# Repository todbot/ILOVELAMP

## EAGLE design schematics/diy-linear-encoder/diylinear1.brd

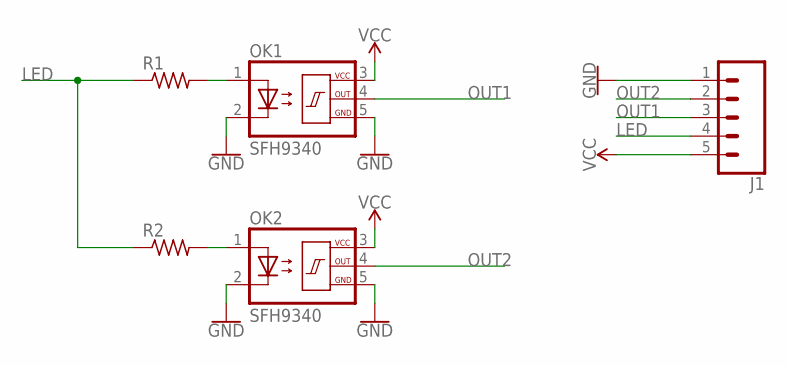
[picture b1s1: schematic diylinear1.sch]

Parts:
J1: CONN_05; 1X05
OK1, OK2: SFH9340
R1, R2: R-US_0204/5; 0204/5

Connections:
GND: J1.1, OK1.2 (C), OK1.5 (GND), OK2.2 (C), OK2.5 (GND)
LED: J1.4, R1.1, R2.1
unnamed: OK1.1 (A), R1.2
unnamed: OK2.1 (A), R2.2
OUT1: J1.3, OK1.4 (OUT)
OUT2: J1.2, OK2.4 (OUT)
VCC: J1.5, OK1.3 (VCC), OK2.3 (VCC)

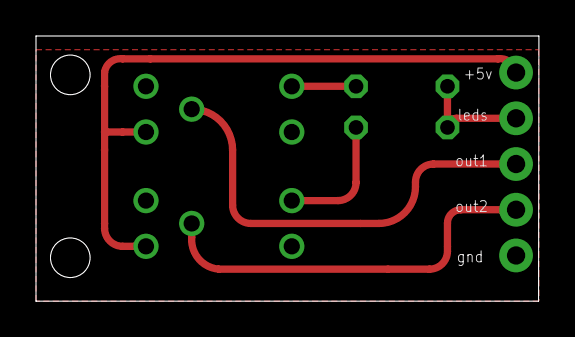
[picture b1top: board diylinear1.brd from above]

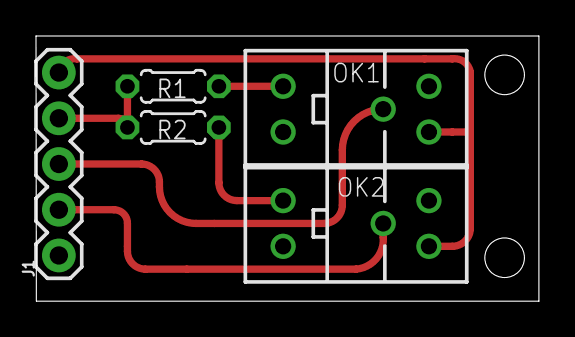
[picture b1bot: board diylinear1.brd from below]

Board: 2 copper layers, 27.9 x 14.7 mm, 5 parts (5 on the bottom side), 7 nets.

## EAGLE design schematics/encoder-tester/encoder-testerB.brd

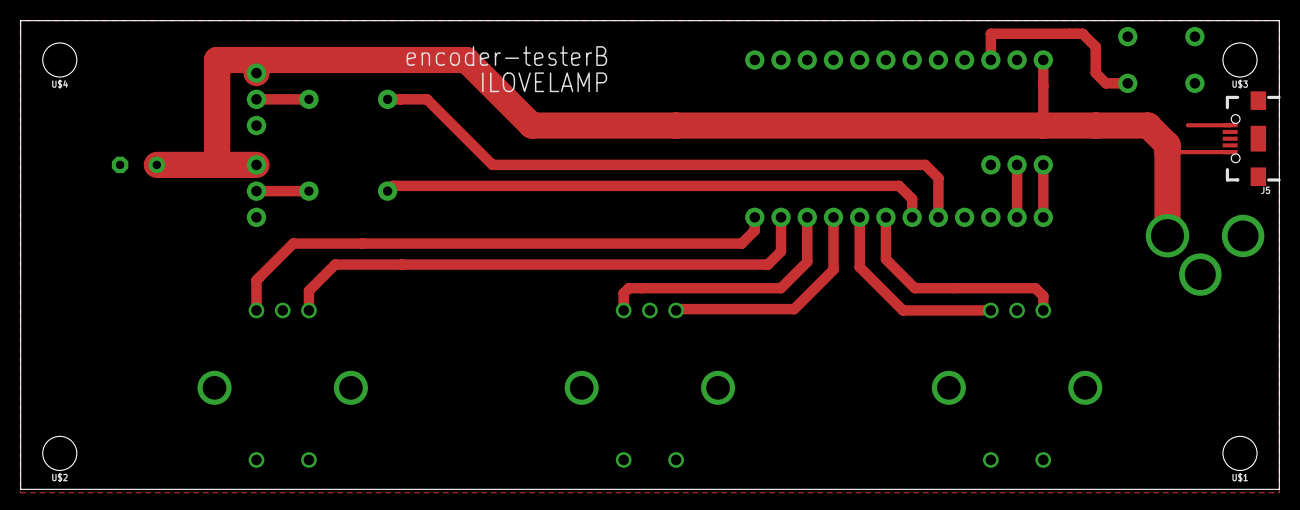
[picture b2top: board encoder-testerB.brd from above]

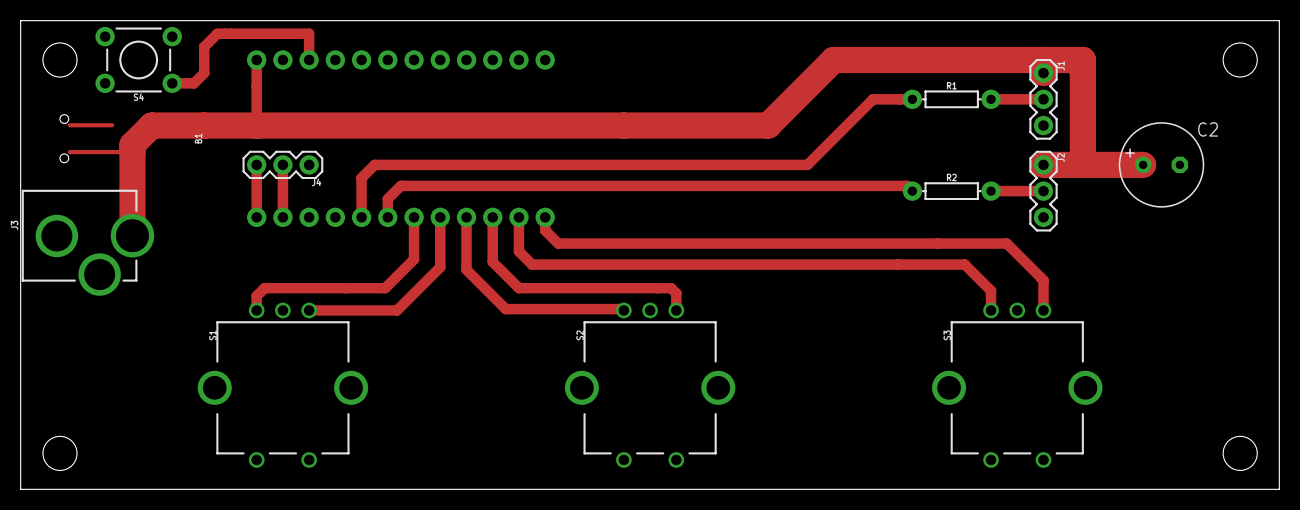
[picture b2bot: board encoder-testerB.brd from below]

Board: 2 copper layers, 121.9 x 45.4 mm, 17 parts (12 on the bottom side), 15 nets.

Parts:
B1: SPARKFUN_PRO_MICRO
C2: E3,5-8
J1, J2, J4: 1X03
J3: POWER_JACKPTH_LOCK; POWER_JACK_PTH_LOCK
J5: USB-B-MICRO-SMD
R1, R2: 1k; AXIAL-0.3
S1, S2, S3: ENCODER-SWITCH; ROTARY_ENC_PLAIN
S4: tact6mm; TACTILE_SWITCH_PTH_6.0MM
U$1, U$2, U$3, U$4: STAND-OFF

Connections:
ENC1A: B1.8, S1.A
ENC1B: B1.7, S1.B
ENC2A: B1.10, S2.A
ENC2B: B1.9, S2.B
ENC3A: B1.12, S3.A
ENC3B: B1.11, S3.B
GND: B1.3, B1.4, B1.23, C2.-, J1.3, J2.3, J3.GND, J3.GNDBREAK, J4.1, J5.GND, S1.C, S2.C, S3.C, S3.SW+, S4.3
LED1: B1.5, R1.P$1
LED2: B1.6, R2.P$1
unnamed: J1.2, R1.P$2
unnamed: J2.2, R2.P$2
unnamed: B1.2, J4.2
unnamed: B1.1, J4.3
RESET: B1.22, S4.1
VIN: B1.24, C2.+, J1.1, J2.1, J3.PWR, J5.VBUS

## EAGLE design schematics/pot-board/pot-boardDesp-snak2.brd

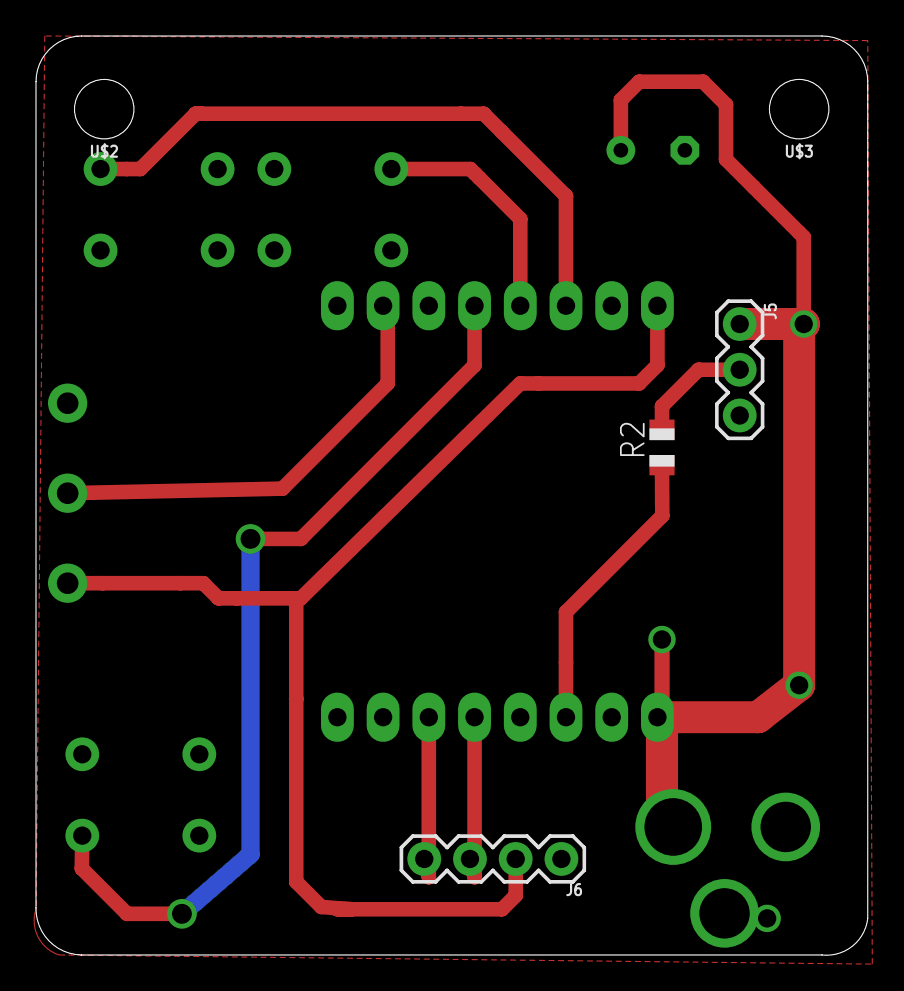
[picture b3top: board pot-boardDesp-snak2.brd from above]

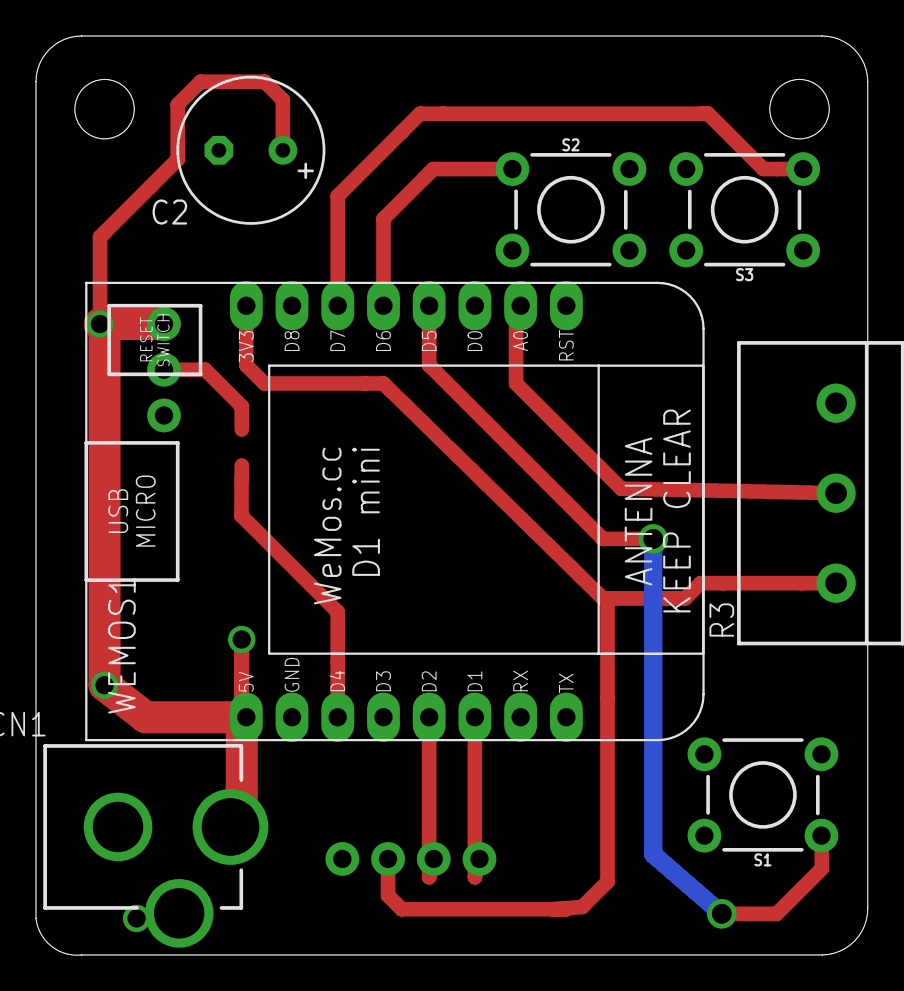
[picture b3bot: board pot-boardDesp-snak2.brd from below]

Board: 2 copper layers, 46.2 x 51.1 mm, 12 parts (7 on the bottom side), 11 nets.

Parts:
C2: E3,5-8
CN1: DCJACK_2MM_PTH
J5: 1X03
J6: 1X04
R2: 500; R0805
R3: 3RP/1610N
S1, S2, S3: tact6mm; TACTILE_SWITCH_PTH_6.0MM
U$2, U$3: STAND-OFF
WEMOS1: WEMOS-D1-MINI

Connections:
+3V3: J6.2, R3.1, WEMOS1.3V3
A0: R3.2, WEMOS1.A0
BUTT1: S1.1, WEMOS1.D5
BUTT2: S2.1, WEMOS1.D6
BUTT3: S3.3, WEMOS1.D7
GND: C2.-, CN1.GND, CN1.GNDBREAK, J5.3, J6.1, R3.3, S1.3, S2.3, S3.1, WEMOS1.GND
LED1: R2.1, WEMOS1.D4
LED1O: J5.2, R2.2
SCL: J6.4, WEMOS1.D1
SDA: J6.3, WEMOS1.D2
VIN: C2.+, CN1.PWR, J5.1, WEMOS1.5V

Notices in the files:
parts and their libraries:
SparkFun-Connectors: Licensing: Creative Commons ShareAlike 4.0 International - https://creativecommons.org/licenses/by-sa/4.0
